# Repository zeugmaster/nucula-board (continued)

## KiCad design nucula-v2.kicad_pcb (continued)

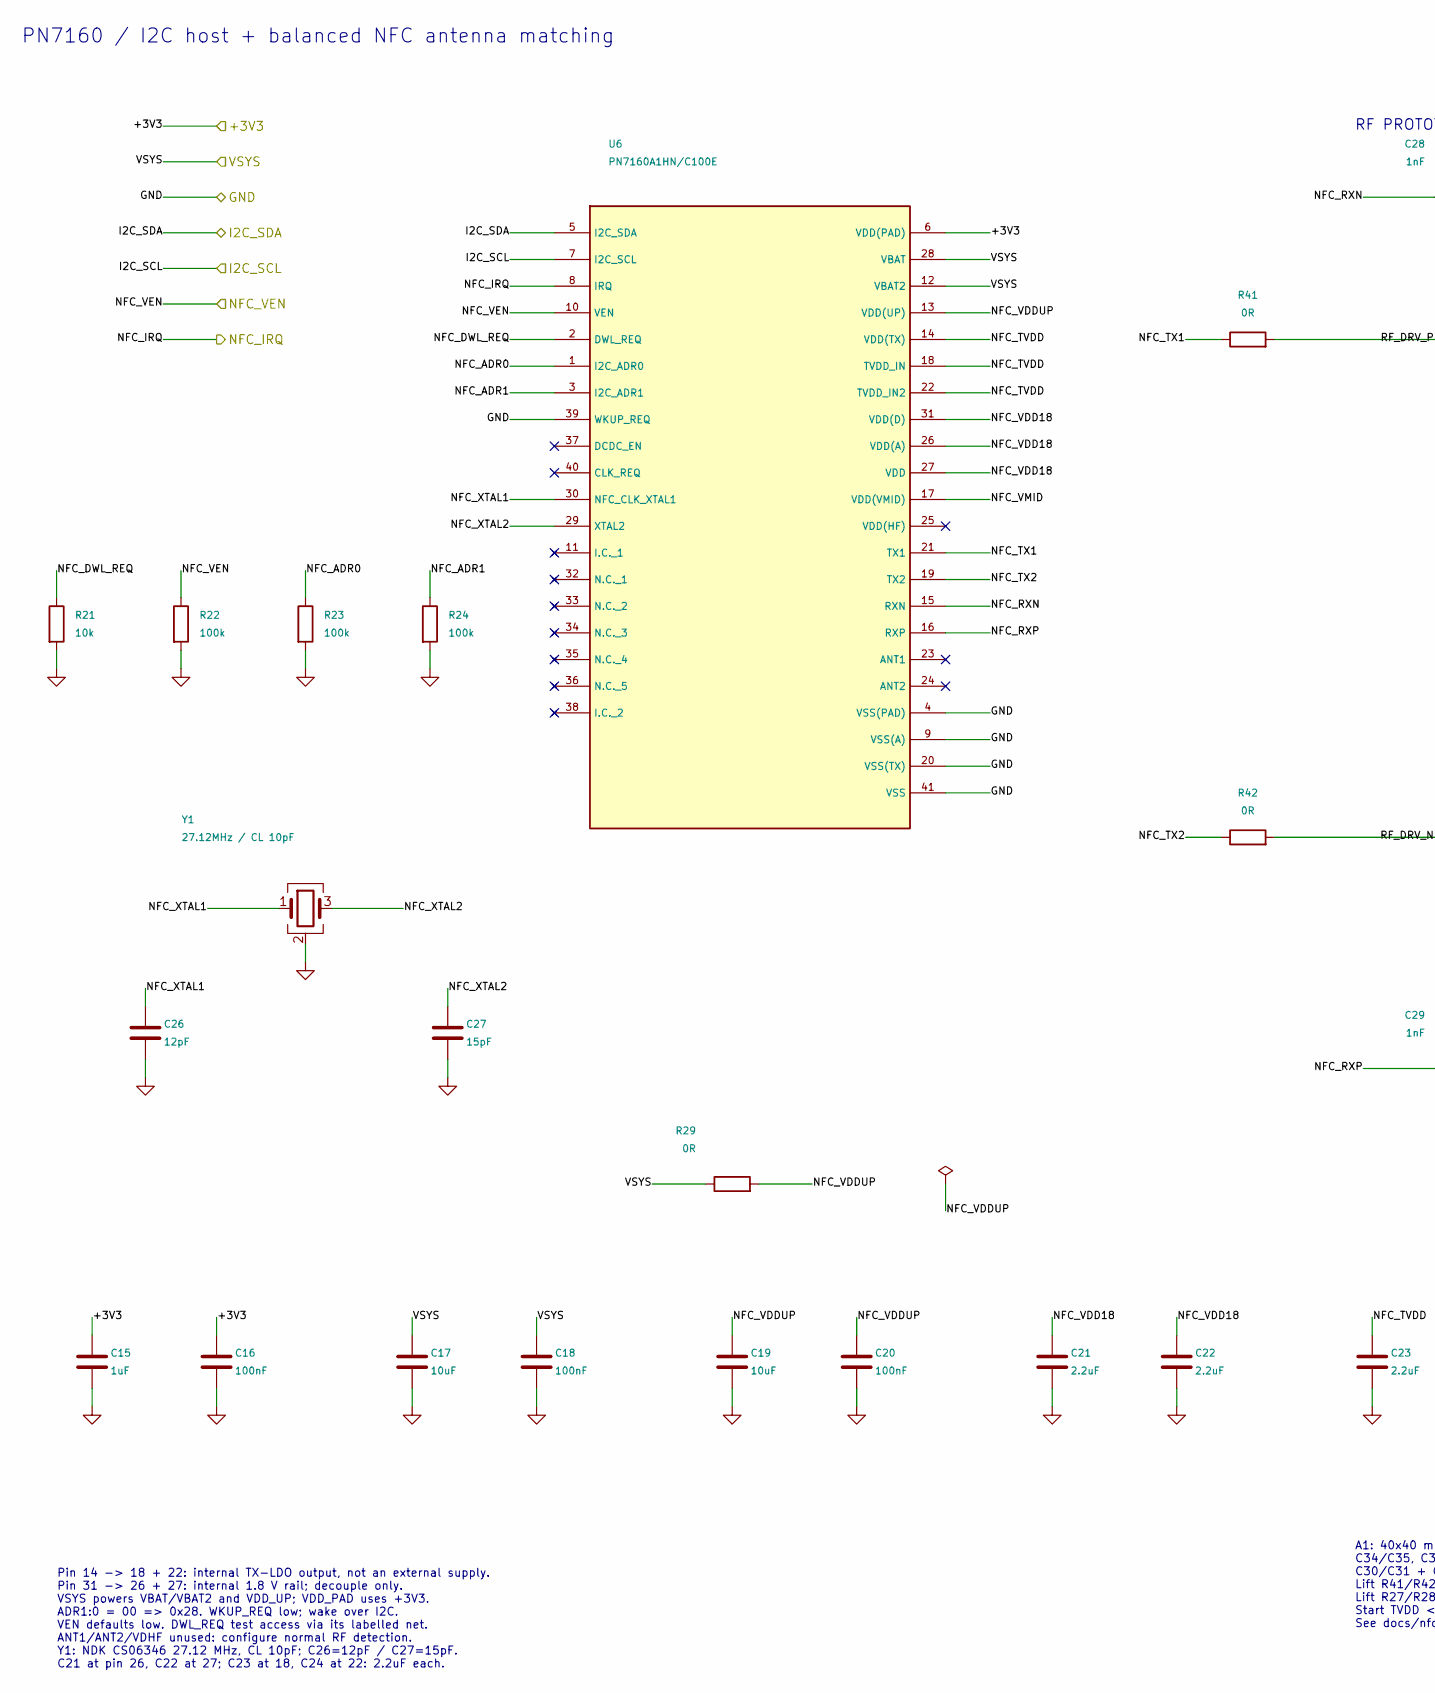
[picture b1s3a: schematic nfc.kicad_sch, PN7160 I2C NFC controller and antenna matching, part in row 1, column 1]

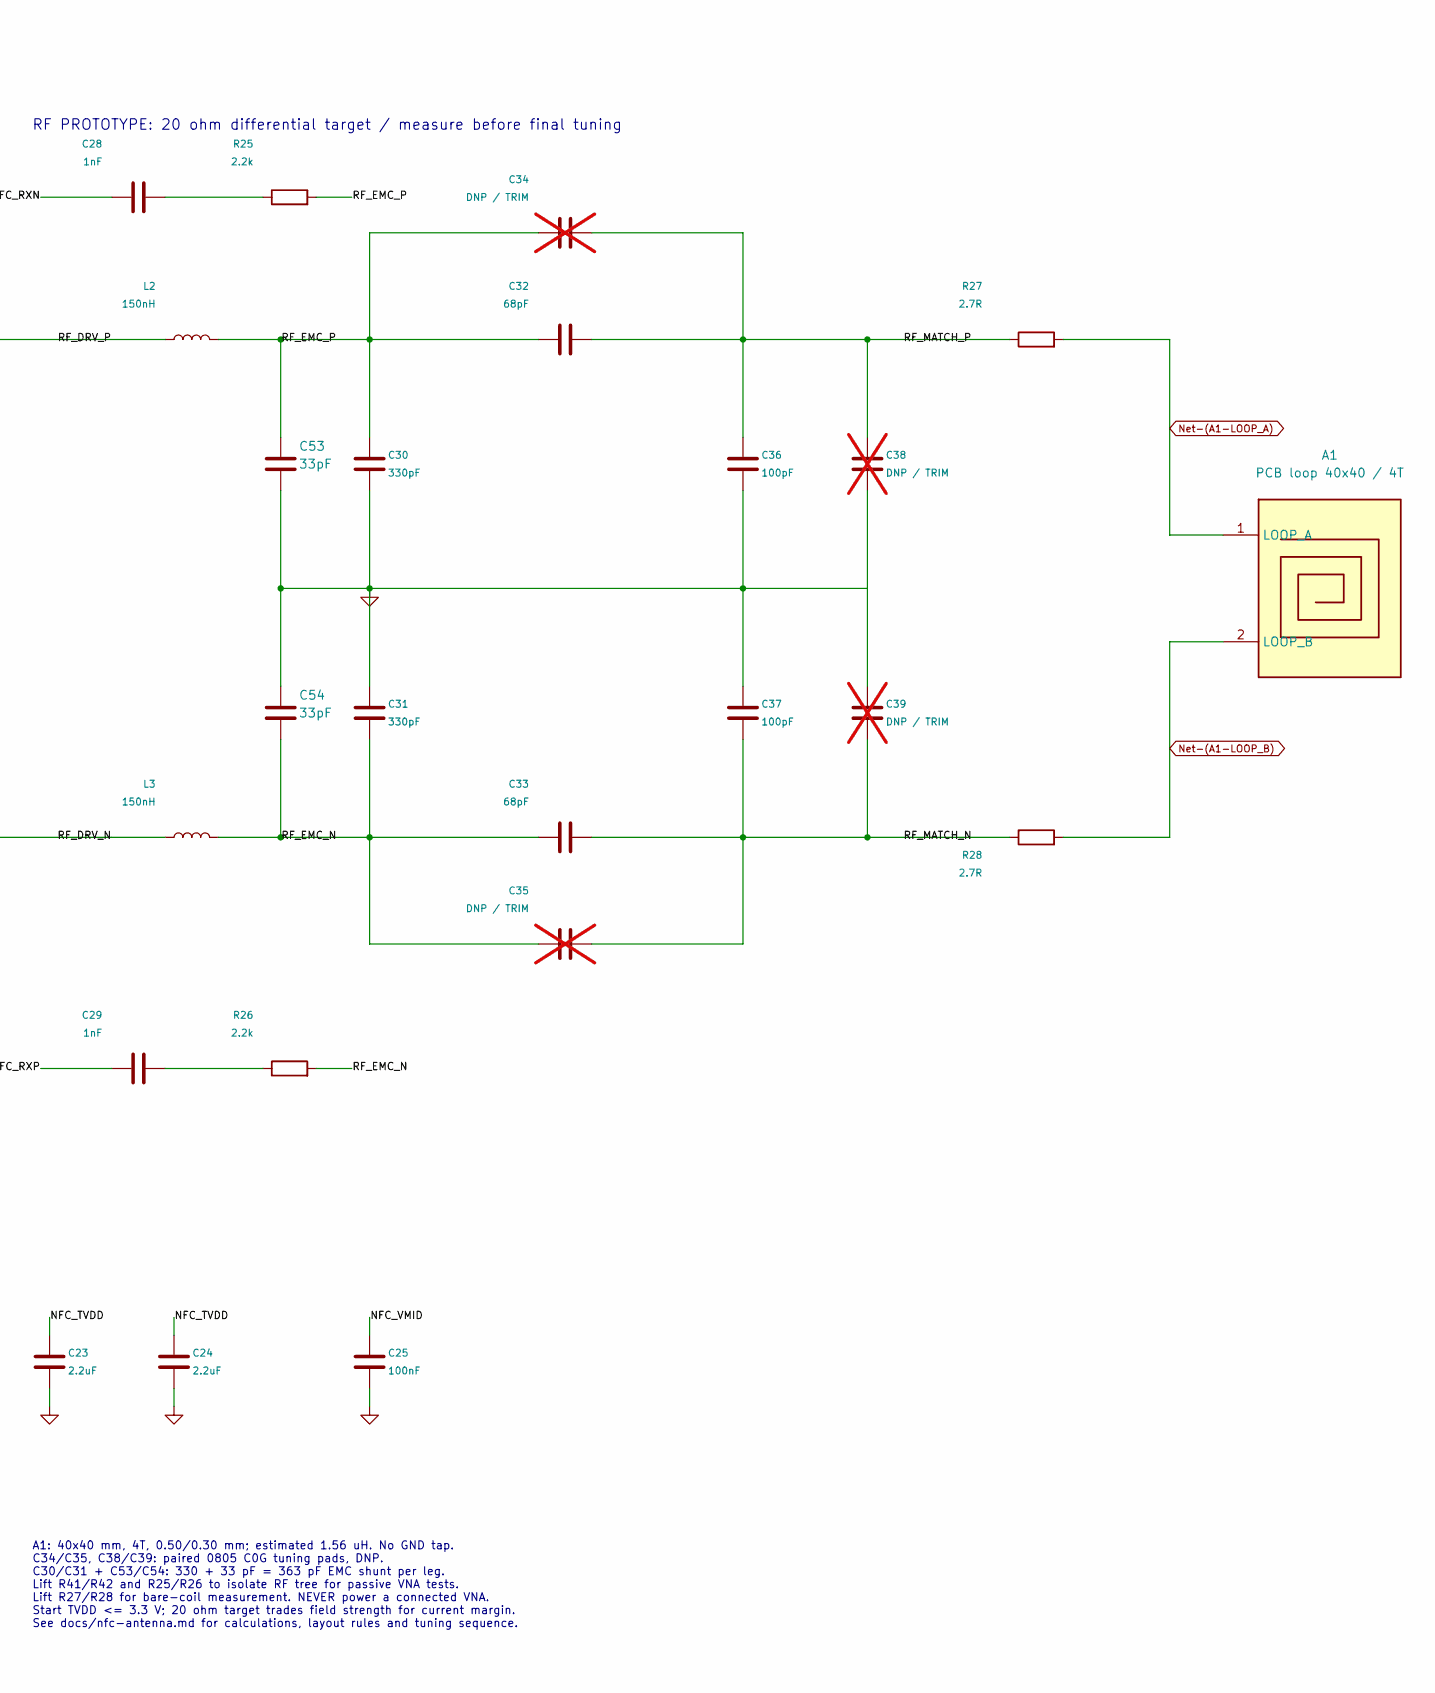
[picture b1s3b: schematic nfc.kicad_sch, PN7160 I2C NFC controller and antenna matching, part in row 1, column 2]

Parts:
A1: PCB loop 40x40 / 4T; NFC_PCB_Loop_40x40_4T_W0.50_S0.30_InsideFeed
C15: 1uF; C_0805_2012Metric; Voltage 50 V; Tolerance 10%; MPN CL21B105KBFNNNE; LCSC C28323
C16, C18, C20, C25: 100nF; C_0603_1608Metric; Voltage 50 V; Tolerance 10%; MPN CL10B104KB8NNNL; LCSC C913912
C17, C19: 10uF; C_1206_3216Metric; Voltage 25 V; Tolerance 10%; MPN CL31B106KAHNNNE; LCSC C14860
C21, C22, C23, C24: 2.2uF; C_0805_2012Metric; Voltage 25 V; Tolerance 10%; MPN CL21B225KAFNNNE; LCSC C19110
C26: 12pF; C_0603_1608Metric; Voltage 50 V; Tolerance 5%; MPN CL10C120JB8NNNC; LCSC C38523
C27: 15pF; C_0603_1608Metric; Voltage 50 V; Tolerance 5%; MPN CL10C150JB8NNNC; LCSC C1644
C28, C29: 1nF; C_0805_2012Metric_Pad1.18x1.45mm_HandSolder; Voltage 100 V; Tolerance 5%; MPN CC0805JRNPO0BN102; LCSC C326940
C30, C31: 330pF; C_0805_2012Metric_Pad1.18x1.45mm_HandSolder; Voltage 100 V; Tolerance 1%; MPN CC0805FRNPO0BN331; LCSC C527075
C32, C33: 68pF; C_0805_2012Metric_Pad1.18x1.45mm_HandSolder; Voltage 100 V; Tolerance 1%; MPN CC0805FRNPO0BN680; LCSC C576904
C34, C35, C38, C39: DNP / TRIM; C_0805_HandSolder_NoPaste; Voltage 100 V; Tolerance <=2% or +/-0.1pF for small trims; not fitted
C36, C37: 100pF; C_0805_2012Metric_Pad1.18x1.45mm_HandSolder; Voltage 100 V; Tolerance 1%; MPN 0805CG101F101NT; LCSC C464454
C53, C54: 33pF; C_0805_2012Metric_Pad1.18x1.45mm_HandSolder; Voltage 100 V; Tolerance 5%; MPN CC0805JRNPO0BN330; LCSC C309485
L2, L3: 150nH; L_Coilcraft_0805CS_RevALands; Tolerance 2%; MPN 0805CS-151XGLC; LCSC C38190612
R21: 10k; R_0603_1608Metric; Tolerance 1%; Rating 0.1 W; MPN 0603WAF1002T5E; LCSC C25804
R22, R23, R24: 100k; R_0603_1608Metric; Tolerance 1%; Rating 0.1 W; MPN 0603WAF1003T5E; LCSC C25803
R25, R26: 2.2k; R_0805_2012Metric_Pad1.20x1.40mm_HandSolder; Tolerance 1%; Rating 0.125 W; MPN 0805W8F2201T5E; LCSC C17520
R27, R28: 2.7R; R_1206_3216Metric_Pad1.30x1.75mm_HandSolder; Tolerance 1%; Rating 0.75 W P70 only with Rth <=110 K/W; lim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; MPN CRCW12062R70FKEAHP; LCSC C2079511
R29: 0R; R_0603_1608Metric; Tolerance 1%; Rating 0.1 W; MPN 0603WAF0000T5E; LCSC C21189
R41, R42: 0R; R_0805_2012Metric_Pad1.20x1.40mm_HandSolder; Rating Jumper: 2 A rated; initial R <50 mOhm; 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; Tolerance Jumper; MPN RC0805JR-070RL; LCSC C96345
U6: PN7160A1HN/C100E; PN7160A1HN_C100E; MPN PN7160A1HN/C100E; LCSC C3303788
Y1: 27.12MHz / CL 10pF; Crystal_NDK_NX2016SA_2.0x1.6mm; MPN NX2016SA-27.12MHZ-EXS00A-CS06346; LCSC C3008209

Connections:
/+3V3: C15.1, C16.1, U6.6 (VDD(PAD)); also elsewhere on the board
/I2C_SCL: U6.7 (I2C_SCL); also elsewhere on the board
/I2C_SDA: U6.5 (I2C_SDA); also elsewhere on the board
/NFC / PN7160 / 0x28/NFC_ADR0: R23.1, U6.1 (I2C_ADR0)
/NFC / PN7160 / 0x28/NFC_ADR1: R24.1, U6.3 (I2C_ADR1)
/NFC / PN7160 / 0x28/NFC_DWL_REQ: R21.1, U6.2 (DWL_REQ)
/NFC / PN7160 / 0x28/NFC_RXN: C28.1, U6.15 (RXN)
/NFC / PN7160 / 0x28/NFC_RXP: C29.1, U6.16 (RXP)
/NFC / PN7160 / 0x28/NFC_TVDD: C23.1, C24.1, U6.14 (VDD(TX)), U6.18 (TVDD_IN), U6.22 (TVDD_IN2)
/NFC / PN7160 / 0x28/NFC_TX1: R41.1, U6.21 (TX1)
/NFC / PN7160 / 0x28/NFC_TX2: R42.1, U6.19 (TX2)
/NFC / PN7160 / 0x28/NFC_VDD18: C21.1, C22.1, U6.26 (VDD(A)), U6.27 (VDD), U6.31 (VDD(D))
/NFC / PN7160 / 0x28/NFC_VDDUP: C19.1, C20.1, R29.2, U6.13 (VDD(UP))
/NFC / PN7160 / 0x28/NFC_VMID: C25.1, U6.17 (VDD(VMID))
/NFC / PN7160 / 0x28/NFC_XTAL1: C26.1, U6.30 (NFC_CLK_XTAL1), Y1.1
/NFC / PN7160 / 0x28/NFC_XTAL2: C27.1, U6.29 (XTAL2), Y1.3
/NFC / PN7160 / 0x28/RF_DRV_N: L3.1, R42.2
/NFC / PN7160 / 0x28/RF_DRV_P: L2.1, R41.2
/NFC / PN7160 / 0x28/RF_EMC_N: C31.2, C33.1, C35.1, C54.2, L3.2, R26.2
/NFC / PN7160 / 0x28/RF_EMC_P: C30.1, C32.1, C34.1, C53.1, L2.2, R25.2
/NFC / PN7160 / 0x28/RF_MATCH_N: C33.2, C35.2, C37.2, C39.2, R28.1
/NFC / PN7160 / 0x28/RF_MATCH_P: C32.2, C34.2, C36.1, C38.1, R27.1
/NFC_IRQ: U6.8 (IRQ); also elsewhere on the board
/NFC_VEN: R22.1, U6.10 (VEN); also elsewhere on the board
/VSYS: C17.1, C18.1, R29.1, U6.12 (VBAT2), U6.28 (VBAT); also elsewhere on the board
GND: C15.2, C16.2, C17.2, C18.2, C19.2, C20.2, C21.2, C22.2, C23.2, C24.2, C25.2, C26.2, C27.2, C30.2, C31.1, C36.2, C37.1, C38.2, C39.1, C53.2, C54.1, R21.2, R22.2, R23.2, R24.2, U6.4 (VSS(PAD)), U6.9 (VSS(A)), U6.20 (VSS(TX)), U6.39 (WKUP_REQ), U6.41 (VSS), Y1.2 (G), Y1.4 (G); also elsewhere on the board
unnamed: A1.1 (LOOP_A), R27.2
unnamed: A1.2 (LOOP_B), R28.2
unnamed: C28.2, R25.1
unnamed: C29.2, R26.1

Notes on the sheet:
PN7160 / I2C host + balanced NFC antenna matching
RF PROTOTYPE: 20 ohm differential target / measure before final tuning
Pin 14 -> 18 + 22: internal TX-LDO output, not an external supply. Pin 31 -> 26 + 27: internal 1.8 V rail; decouple only. VSYS powers VBAT/VBAT2 and VDD_UP; VDD_PAD uses +3V3. ADR1:0 = 00 => 0x28. WKUP_REQ low; wake over I2C. VEN defaults low. DWL_REQ test access via its labelled net. ANT1/ANT2/VDH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
A1: 40x40 mm, 4T, 0.50/0.30 mm; estimated 1.56 uH. No GND tap. C34/C35, C38/C39: paired 0805 C0G tuning pads, DNP. C30/C31 + C53/C54: 330 + 33 pF = 363 pF EMC shunt per leg. Lift R41/R42 and R25/R26 to isolate RF tree for passive VNA tests. Lift R27/R28 for bare-coil measurement. NEVER power a conn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

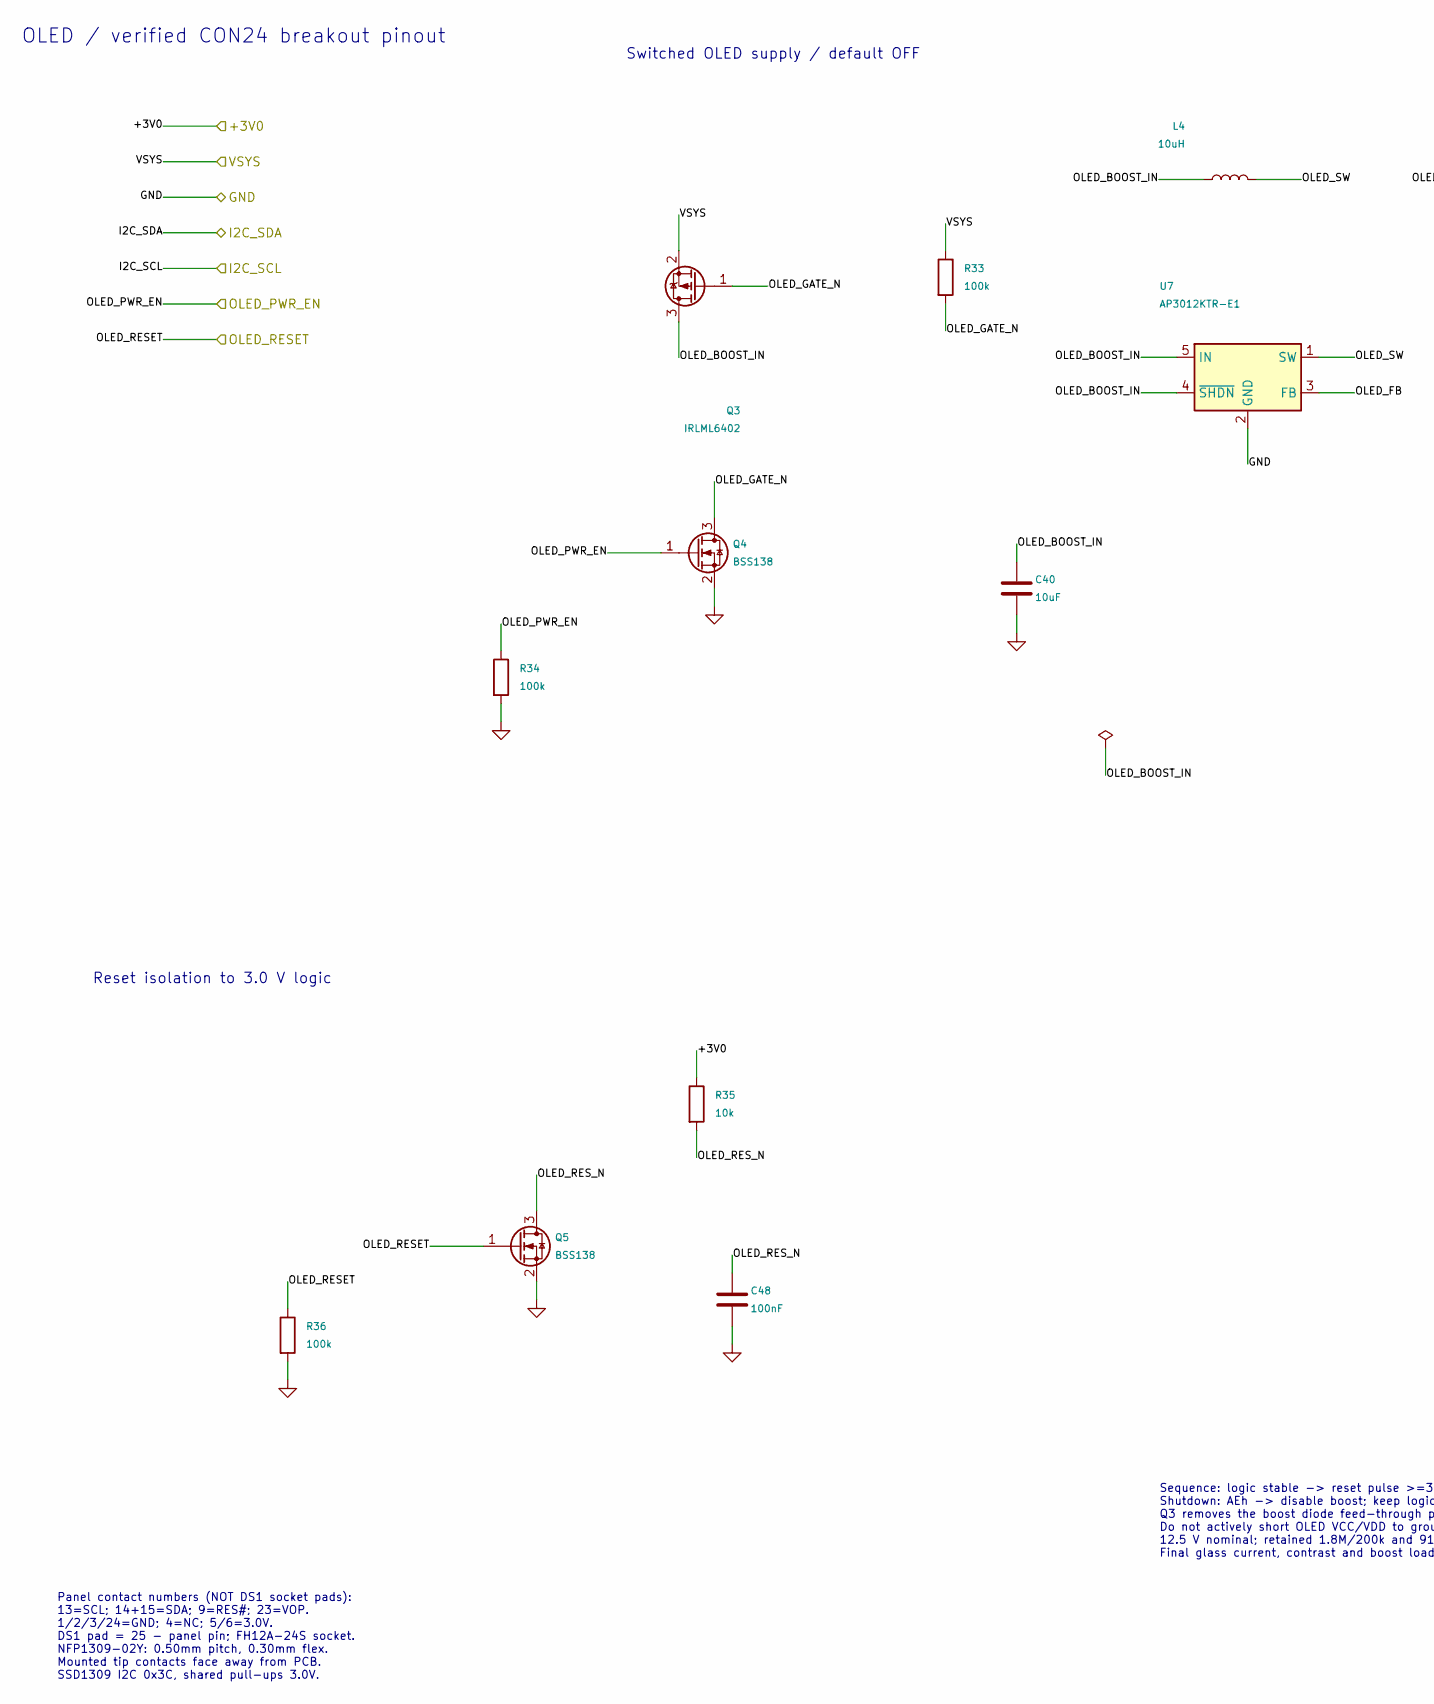
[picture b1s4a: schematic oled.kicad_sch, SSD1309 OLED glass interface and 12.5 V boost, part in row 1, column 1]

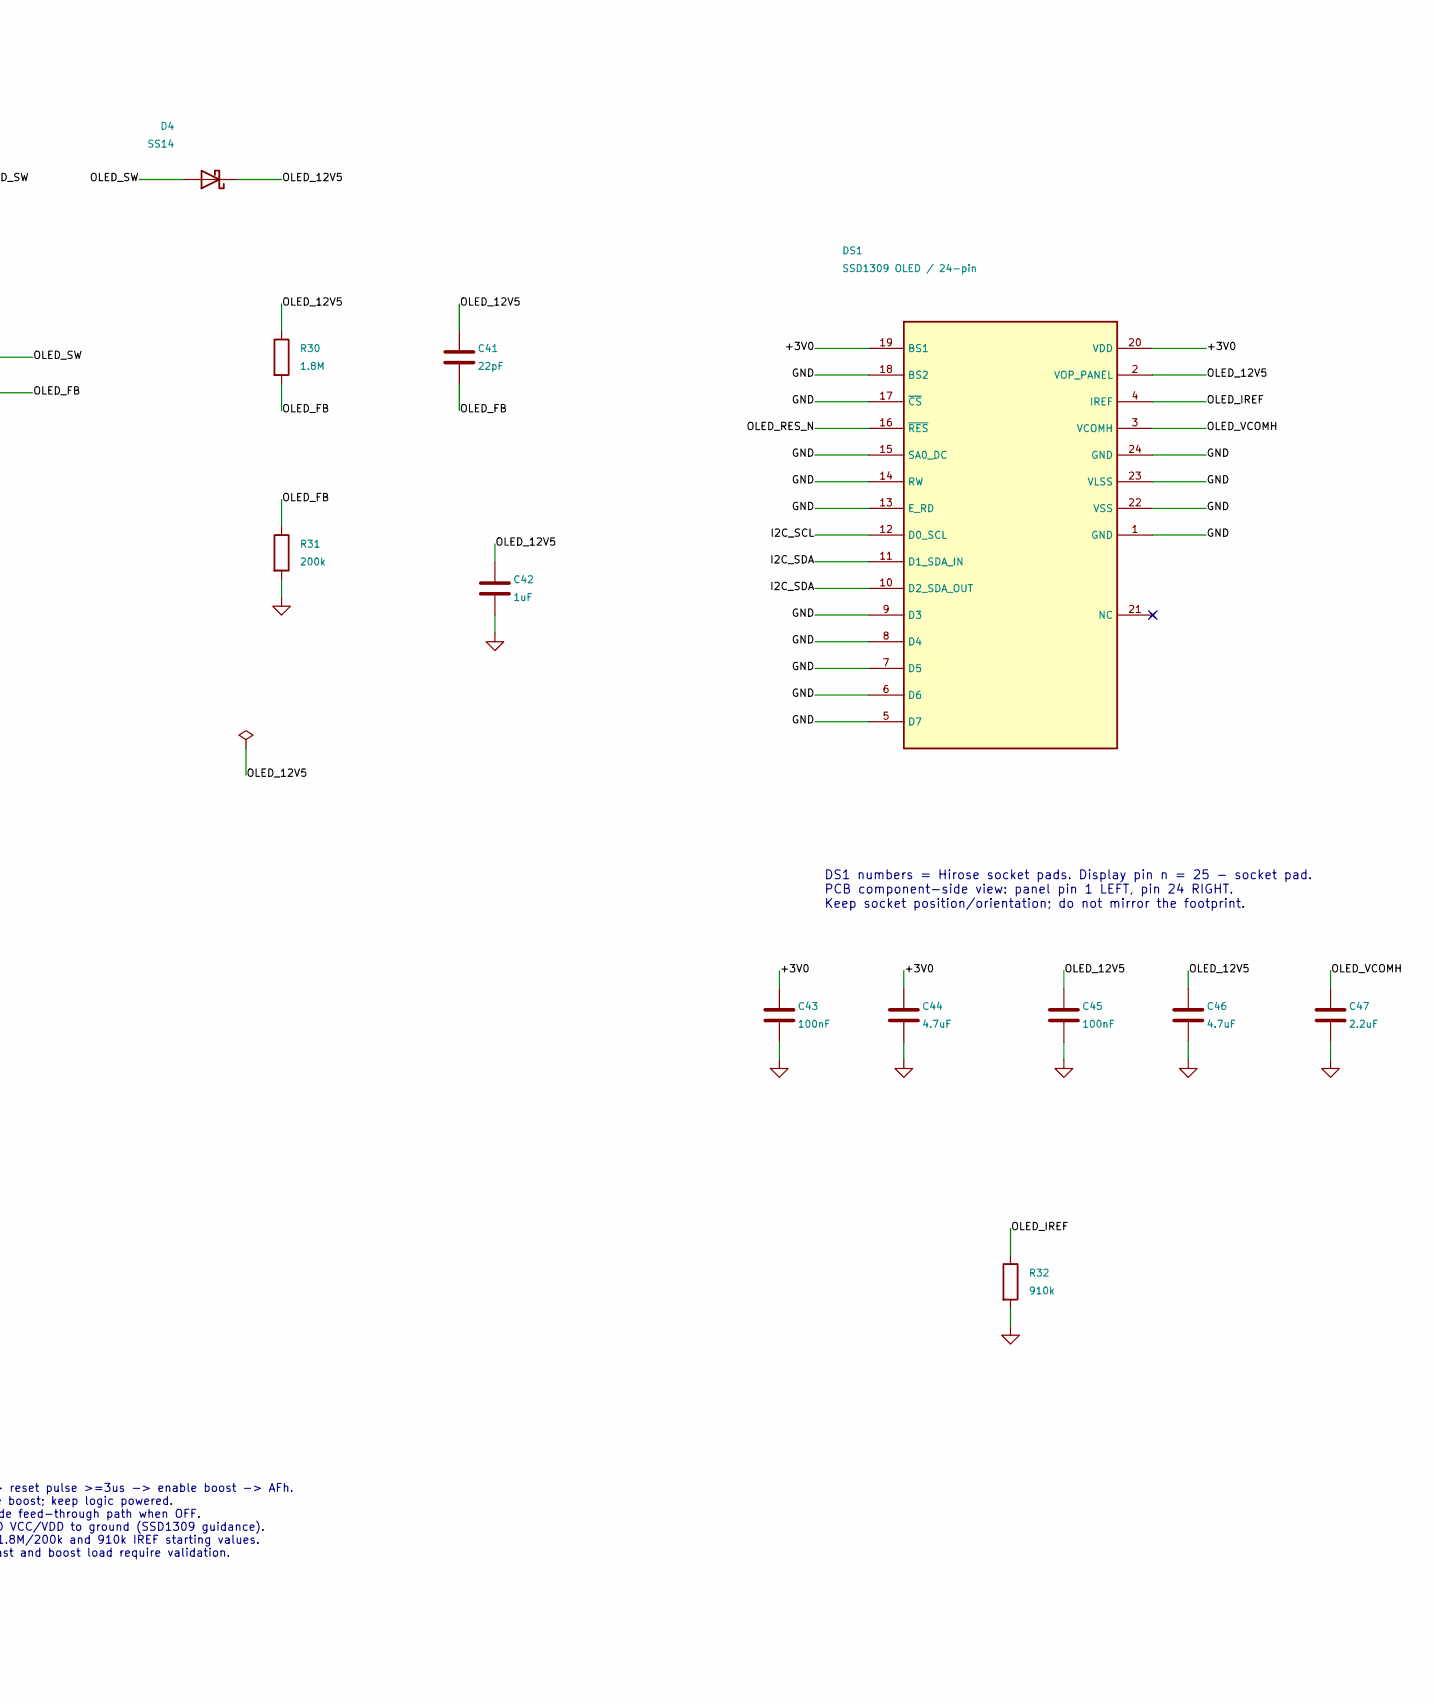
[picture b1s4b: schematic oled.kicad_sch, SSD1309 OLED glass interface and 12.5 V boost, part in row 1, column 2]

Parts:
C40: 10uF; C_1206_3216Metric; Voltage 25 V; Tolerance 10%; MPN CL31B106KAHNNNE; LCSC C14860
C41: 22pF; C_0603_1608Metric; Voltage 50 V; Tolerance 5%; MPN CL10C220JB8NNNC; LCSC C1653
C42: 1uF; C_0805_2012Metric; Voltage 50 V; Tolerance 10%; MPN CL21B105KBFNNNE; LCSC C28323
C43, C45, C48: 100nF; C_0603_1608Metric; Voltage 50 V; Tolerance 10%; MPN CL10B104KB8NNNL; LCSC C913912
C44: 4.7uF; C_0805_2012Metric; Voltage 25 V; Tolerance 10%; MPN CL21B475KAFNNNE; LCSC C98195
C46: 4.7uF; C_1206_3216Metric; Voltage 50 V; Tolerance 10%; MPN CL31B475KBHNNNE; LCSC C51205
C47: 2.2uF; C_0805_2012Metric; Voltage 25 V; Tolerance 10%; MPN CL21B225KAFNNNE; LCSC C19110
D4: SS14; D_SMA; MPN SS14-E3/61T; LCSC C47460
DS1: SSD1309 OLED / 24-pin; Hirose_FH12A-24S-0.5SH_1x24-1MP_P0.50mm_Horizontal; MPN FH12A-24S-0.5SH(55); LCSC C506794
L4: 10uH; L_Coilcraft_LPS4018; Rating Isat 1.1 A at 10% drop; Irms 0.9 A at 2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; MPN LPS4018-103MRC; LCSC C6127589
Q3: IRLML6402; SOT-23; MPN IRLML6402TRPBF; LCSC C2593
Q4, Q5: BSS138; SOT-23; MPN BSS138; LCSC C52895
R30: 1.8M; R_0805_2012Metric; Tolerance 0.1%; Rating 0.1 W; 100 V; 25 ppm/K; MPN CPF0805B1M8E; LCSC C2088132
R31: 200k; R_0603_1608Metric; Tolerance 0.1%; Rating 0.1 W; MPN RT0603BRD07200KL; LCSC C728585
R32: 910k; R_0603_1608Metric; Tolerance 1%; Rating 0.1 W; MPN 0603WAF9103T5E; LCSC C23263
R33, R34, R36: 100k; R_0603_1608Metric; Tolerance 1%; Rating 0.1 W; MPN 0603WAF1003T5E; LCSC C25803
R35: 10k; R_0603_1608Metric; Tolerance 1%; Rating 0.1 W; MPN 0603WAF1002T5E; LCSC C25804
U7: AP3012KTR-E1; SOT-23-5; MPN AP3012KTR-E1; LCSC C460356

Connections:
/+3V0: C43.1, C44.1, DS1.19 (BS1), DS1.20 (VDD), R35.1; also elsewhere on the board
/I2C_SCL: DS1.12 (D0_SCL); also elsewhere on the board
/I2C_SDA: DS1.10 (D2_SDA_OUT), DS1.11 (D1_SDA_IN); also elsewhere on the board
/OLED / SSD1309 / 0x3C/OLED_12V5: C41.1, C42.1, C45.1, C46.1, D4.1 (K), DS1.2 (VOP_PANEL), R30.1
/OLED / SSD1309 / 0x3C/OLED_BOOST_IN: C40.1, L4.1, Q3.3 (D), U7.4 (~SHDN), U7.5 (IN)
/OLED / SSD1309 / 0x3C/OLED_FB: C41.2, R30.2, R31.1, U7.3 (FB)
/OLED / SSD1309 / 0x3C/OLED_GATE_N: Q3.1 (G), Q4.3 (D), R33.2
/OLED / SSD1309 / 0x3C/OLED_IREF: DS1.4 (IREF), R32.1
/OLED / SSD1309 / 0x3C/OLED_RES_N: C48.1, DS1.16 (~RES), Q5.3 (D), R35.2
/OLED / SSD1309 / 0x3C/OLED_SW: D4.2 (A), L4.2, U7.1 (SW)
/OLED / SSD1309 / 0x3C/OLED_VCOMH: C47.1, DS1.3 (VCOMH)
/OLED_PWR_EN: Q4.1 (G), R34.1; also elsewhere on the board
/OLED_RESET: Q5.1 (G), R36.1; also elsewhere on the board
/VSYS: Q3.2 (S), R33.1; also elsewhere on the board
GND: C40.2, C42.2, C43.2, C44.2, C45.2, C46.2, C47.2, C48.2, DS1.1 (GND), DS1.5 (D7), DS1.6 (D6), DS1.7 (D5), DS1.8 (D4), DS1.9 (D3), DS1.13 (E_RD), DS1.14 (RW), DS1.15 (SA0_DC), DS1.17 (~CS), DS1.18 (BS2), DS1.22 (VSS), DS1.23 (VLSS), DS1.24 (GND), Q4.2 (S), Q5.2 (S), R31.2, R32.2, R34.2, R36.2, U7.2 (GND); also elsewhere on the board

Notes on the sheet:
OLED / verified CON24 breakout pinout
Switched OLED supply / default OFF
Reset isolation to 3.0 V logic
Panel contact numbers (NOT DS1 socket pads): 13=SCL; 14+15=SDA; 9=RES#; 23=VOP. 1/2/3/24=GND; 4=NC; 5/6=3.0V. DS1 pad = 25 - panel pin; FH12A-24S socket. NFP1309-02Y: 0.50mm pitch, 0.30mm flex. Mounted tip contacts face away from PCB. SSD1309 I2C 0x3C, shared pull-ups 3.0V.
Sequence: logic stable -> reset pulse >=3us -> enable boost -> AFh. Shutdown: AEh -> disable boost; keep logic powered. Q3 removes the boost diode feed-through path when OFF. Do not actively short OLED VCC/VDD to ground (SSD1309 guidance). 12.5 V nominal; retained 1.8M/200k and 910k IREF starting v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
DS1 numbers = Hirose socket pads. Display pin n = 25 - socket pad. PCB component-side view: panel pin 1 LEFT, pin 24 RIGHT. Keep socket position/orientation; do not mirror the footprint.

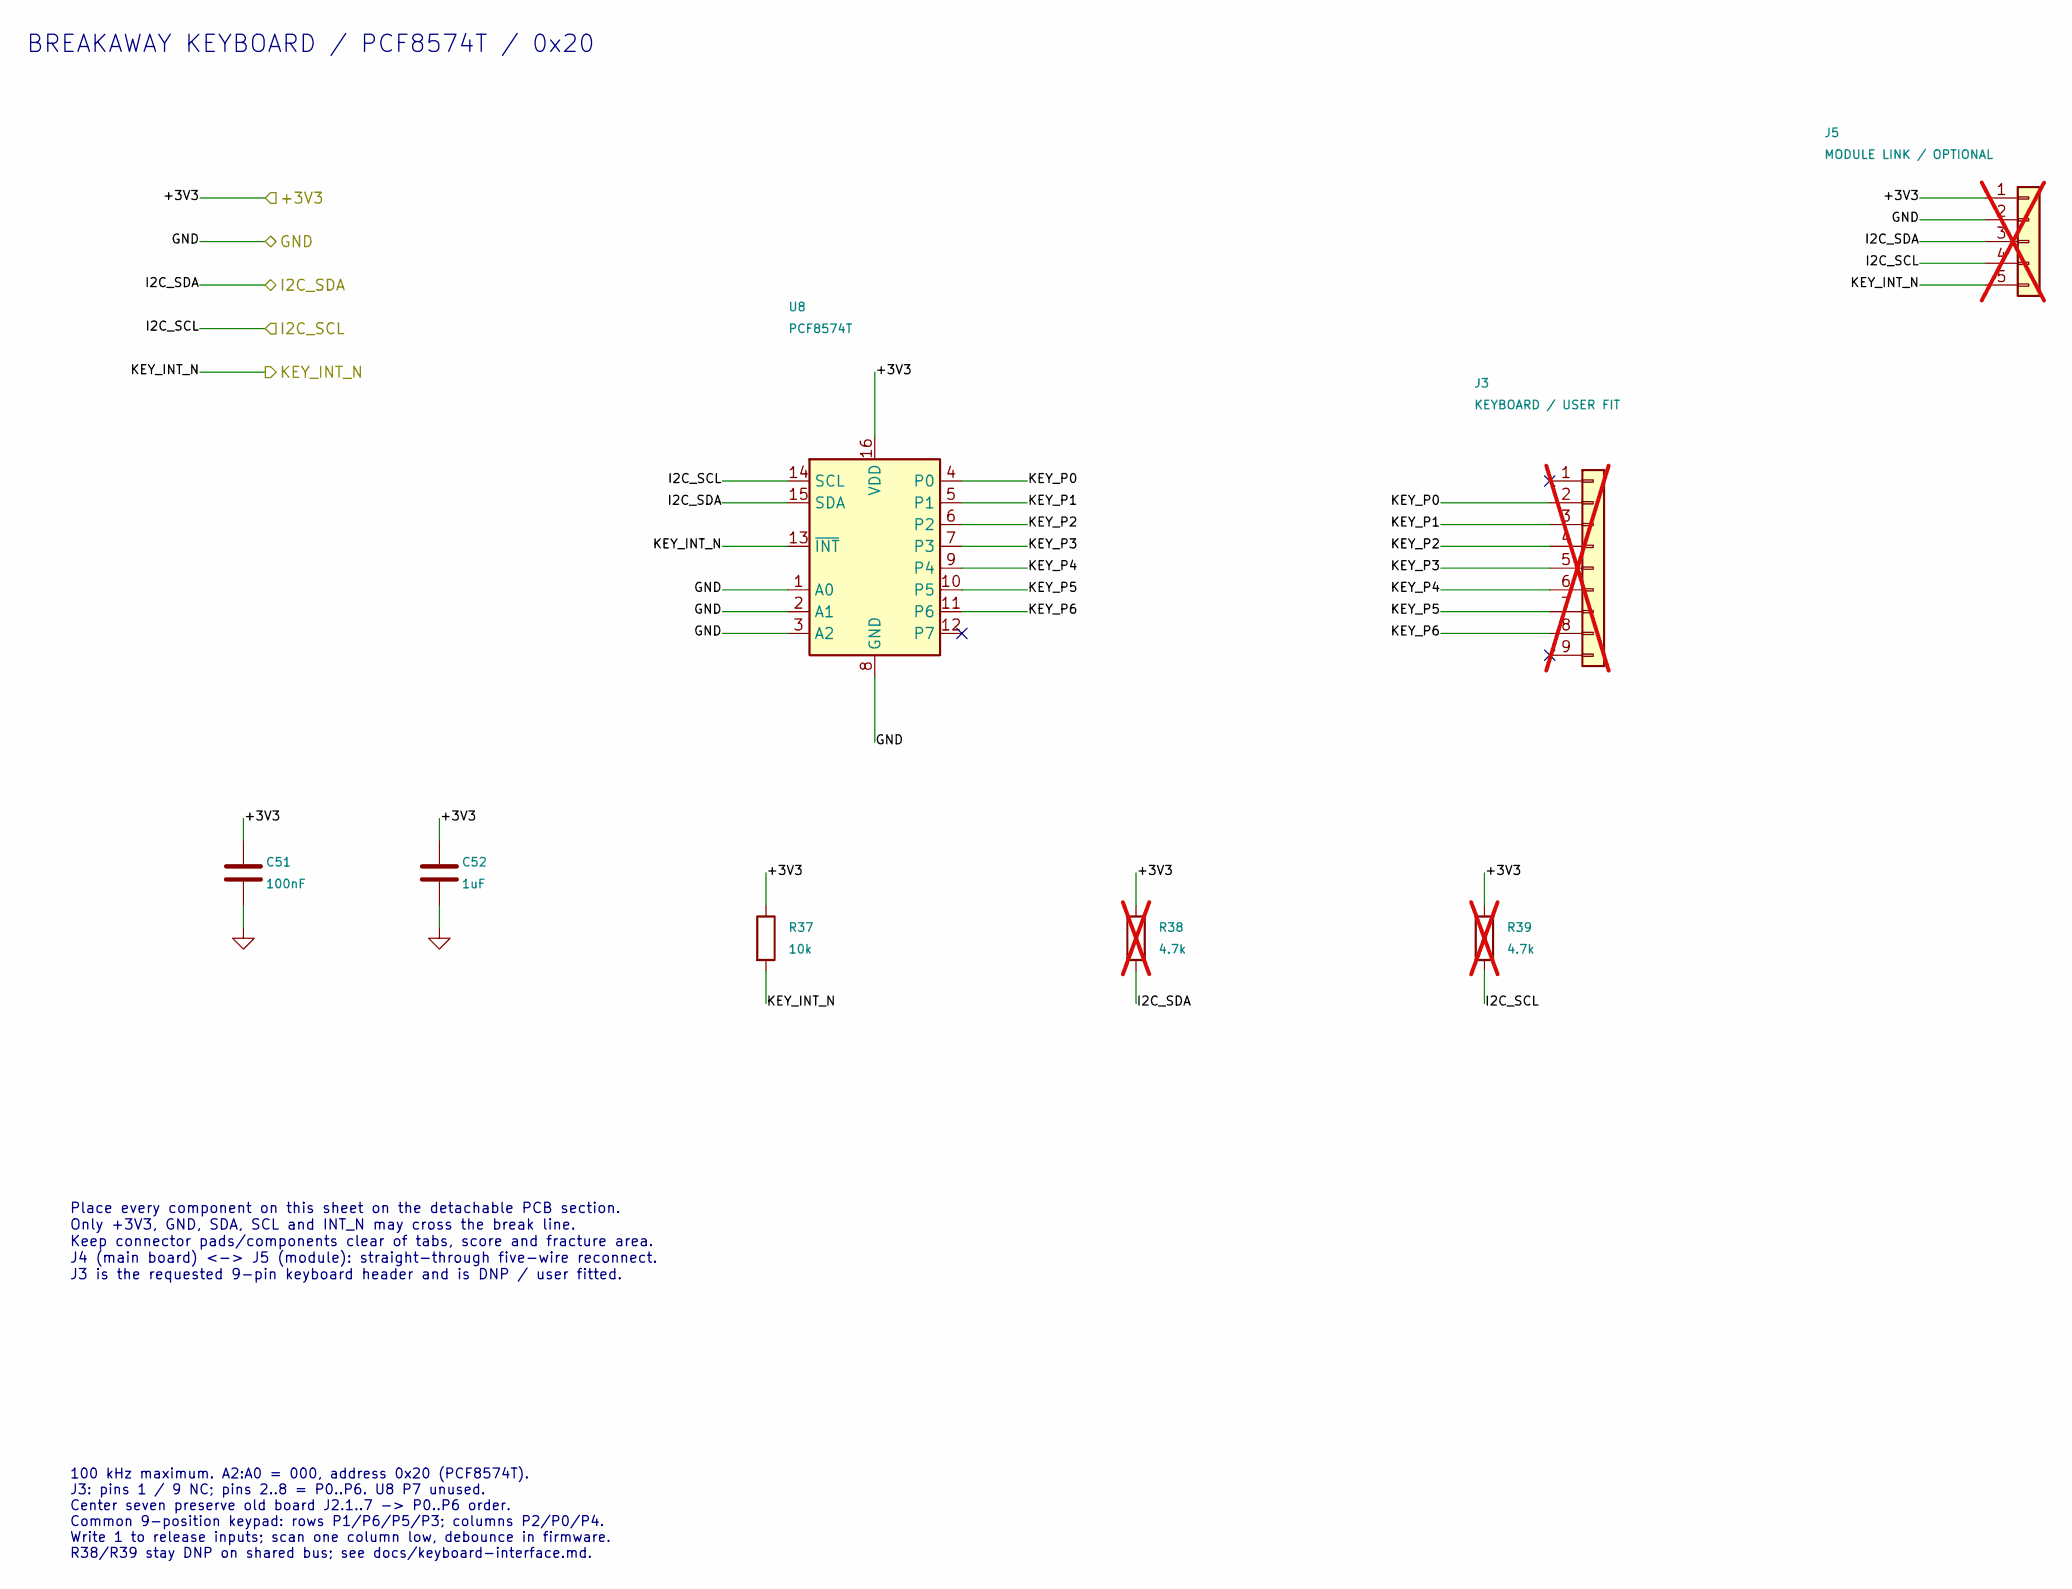
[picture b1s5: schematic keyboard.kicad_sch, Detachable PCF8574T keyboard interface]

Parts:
C51: 100nF; C_0603_1608Metric; Voltage 50 V; Tolerance 10%; MPN CL10B104KB8NNNL; LCSC C913912
C52: 1uF; C_0805_2012Metric; Voltage 50 V; Tolerance 10%; MPN CL21B105KBFNNNE; LCSC C28323
J3: KEYBOARD / USER FIT; PinHeader_1x09_P2.54mm_Vertical; not fitted
J5: MODULE LINK / OPTIONAL; PinHeader_1x05_P2.54mm_Vertical; not fitted
R37: 10k; R_0603_1608Metric; Tolerance 1%; Rating 0.1 W; MPN 0603WAF1002T5E; LCSC C25804
R38, R39: 4.7k; R_0603_1608Metric; Tolerance 1%; Rating 0.1 W; not fitted
U8: PCF8574T; SOIC-16W_7.5x10.3mm_P1.27mm; MPN PCF8574T/3,518; LCSC C7605

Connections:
/+3V3: C51.1, C52.1, J5.1, R37.1, R38.1, R39.1, U8.16 (VDD); also elsewhere on the board
/I2C_SCL: J5.4, R39.2, U8.14 (SCL); also elsewhere on the board
/I2C_SDA: J5.3, R38.2, U8.15 (SDA); also elsewhere on the board
/KEY_INT_N: J5.5, R37.2, U8.13 (~INT); also elsewhere on the board
/Keyboard / breakaway / 0x20/KEY_P0: J3.2, U8.4 (P0)
/Keyboard / breakaway / 0x20/KEY_P1: J3.3, U8.5 (P1)
/Keyboard / breakaway / 0x20/KEY_P2: J3.4, U8.6 (P2)
/Keyboard / breakaway / 0x20/KEY_P3: J3.5, U8.7 (P3)
/Keyboard / breakaway / 0x20/KEY_P4: J3.6, U8.9 (P4)
/Keyboard / breakaway / 0x20/KEY_P5: J3.7, U8.10 (P5)
/Keyboard / breakaway / 0x20/KEY_P6: J3.8, U8.11 (P6)
GND: C51.2, C52.2, J5.2, U8.1 (A0), U8.2 (A1), U8.3 (A2), U8.8 (GND); also elsewhere on the board

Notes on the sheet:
BREAKAWAY KEYBOARD / PCF8574T / 0x20
Place every component on this sheet on the detachable PCB section. Only +3V3, GND, SDA, SCL and INT_N may cross the break line. Keep connector pads/components clear of tabs, score and fracture area. J4 (main board) <-> J5 (module): straight-through five-wire reconnect. J3 is the requested 9-pin key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
100 kHz maximum. A2:A0 = 000, address 0x20 (PCF8574T). J3: pins 1 / 9 NC; pins 2..8 = P0..P6. U8 P7 unused. Center seven preserve old board J2.1..7 -> P0..P6 order. Common 9-position keypad: rows P1/P6/P5/P3; columns P2/P0/P4. Write 1 to release inputs; scan one column low, debounce in firmware. R3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
